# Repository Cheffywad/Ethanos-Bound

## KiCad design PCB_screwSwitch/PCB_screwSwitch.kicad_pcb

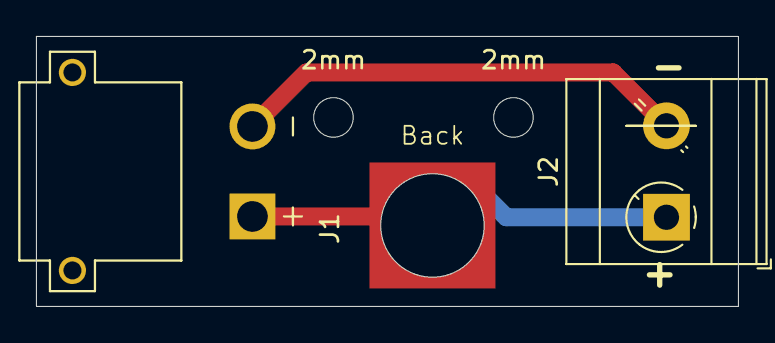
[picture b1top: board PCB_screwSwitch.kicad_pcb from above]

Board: 2 copper layers, 39.0 x 15.0 mm, 7 parts (0 on the bottom side), 3 nets.

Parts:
2mm, 2mm#2: MountingHole_2.2mm_M2
Back: MountingHole_Pad; hole_top
Front: hole_center
H2: MountingHole_Pad; hole_bottom
J1: XT30PW-M; AMASS_XT30PW-M
J2: Screw_Terminal_01x02; TerminalBlock_MetzConnect_Type073_RT02602HBLU_1x02_P5.08mm_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

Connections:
unnamed: Back.1, J1.P
unnamed: H2.1, J2.1
unnamed: J1.N, J2.2

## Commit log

2025-05-09 Rev 2
2025-05-10 Rev 3
    Created rev A of custom PCB Switch
2025-05-21 Rev 3.1
    Minor changes
